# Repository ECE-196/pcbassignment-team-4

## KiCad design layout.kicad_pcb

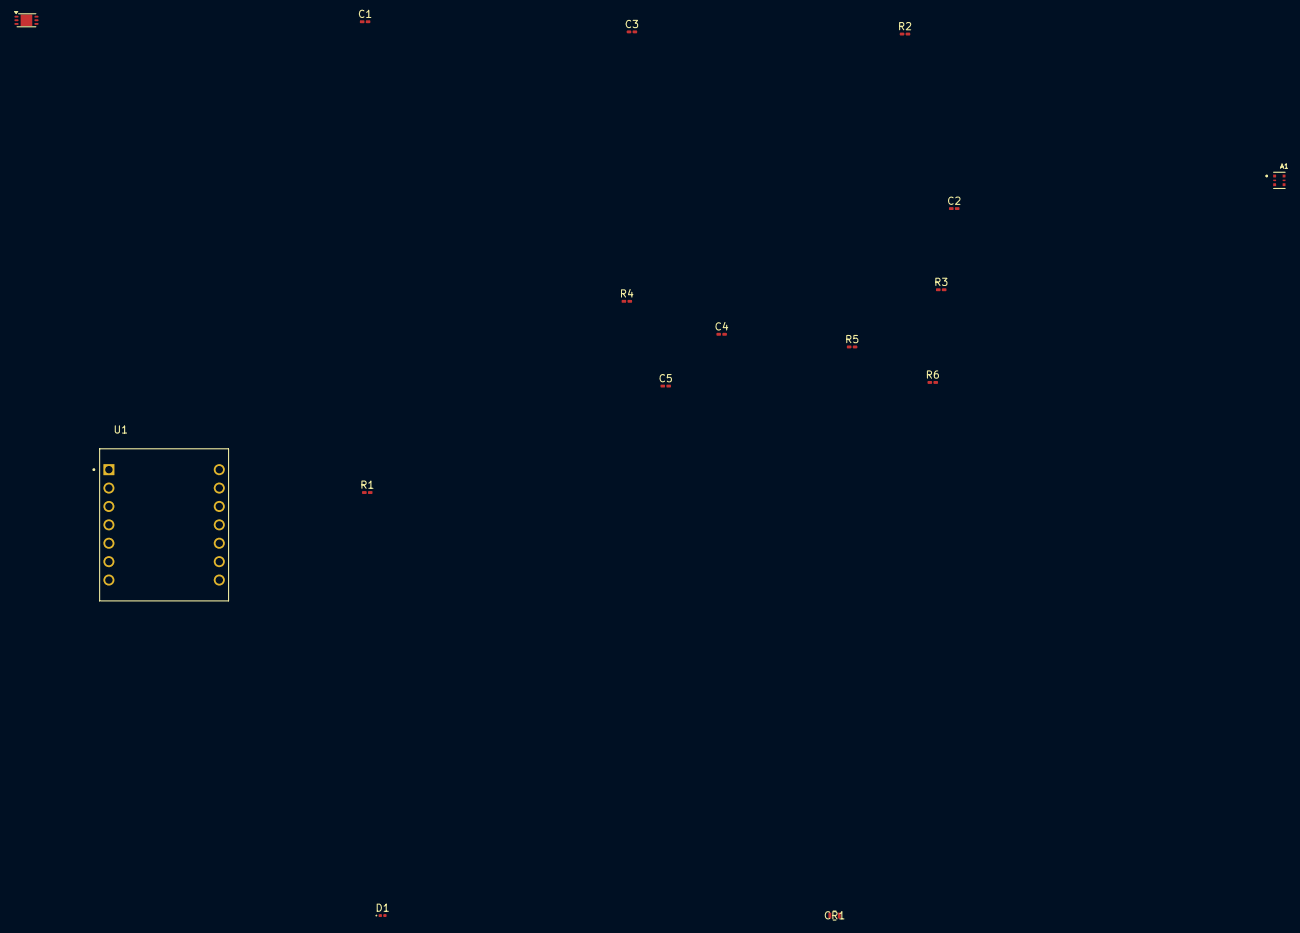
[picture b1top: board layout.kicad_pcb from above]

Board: 2 copper layers, 16 parts (0 on the bottom side), 10 nets, no tracks yet.

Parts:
A1: APDS-9008-020; XDCR_APDS-9008-020
C1, C5: 2.2u; C_0201_0603Metric_Pad0.64x0.40mm_HandSolder
C2, C3, C4: 4.7u; C_0201_0603Metric_Pad0.64x0.40mm_HandSolder
CR1: CD0603-B0240R; DIODE_CD0603-B0240R_BRN
D1: AM2520ZGC09; LED_0201_0603Metric
R1: 470; R_0201_0603Metric_Pad0.64x0.40mm_HandSolder
R2: 12K; R_0201_0603Metric_Pad0.64x0.40mm_HandSolder
R3: 10K; R_0201_0603Metric_Pad0.64x0.40mm_HandSolder
R4, R5: 100K; R_0201_0603Metric_Pad0.64x0.40mm_HandSolder
R6: 3.3M; R_0201_0603Metric_Pad0.64x0.40mm_HandSolder
U1: 102010388; MODULE_102010388
U2: MCP6001-OT; HVSOF6

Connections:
GND: A1.4 (GND), C1.1, C3.2, R1.1, R2.1, R5.1, U1.13 (GND), U2.2 (V-)
unnamed: A1.6 (OUT), C2.1, R2.2
unnamed: C2.2, C3.1, C4.1
unnamed: C4.2, C5.1, R3.2
unnamed: D1.1 (K), R1.2
unnamed: C5.2, R4.1, R5.2, U2.3 (+)
unnamed: R3.1, R6.2, U2.4 (-)
unnamed: CR1.1, U2.5 (V+)
OUTPUT: R6.1, U1.1 (PA02_A0_D0), U2.1
VCC: A1.1 (VCC), C1.2, CR1.2, D1.2 (A), R4.2, U1.14 (5V)

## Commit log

2024-04-26 add deadline
2024-04-29 initial_schematic
2024-05-01 update the layout and the schematic
2024-05-04 updated changelog
    .changelog
2024-05-04 PCB and Export zip
